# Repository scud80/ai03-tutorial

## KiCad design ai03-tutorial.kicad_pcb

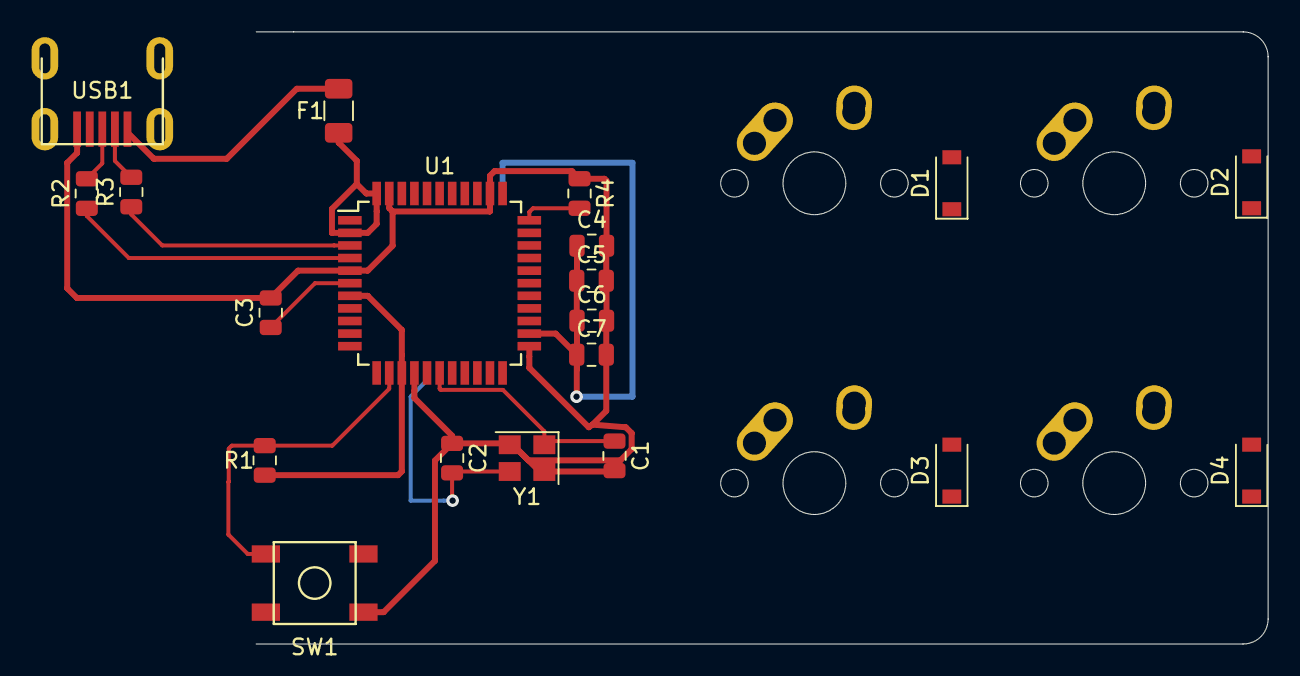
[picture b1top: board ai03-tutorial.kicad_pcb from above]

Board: 2 copper layers, 64.3 x 38.9 mm, 24 parts (0 on the bottom side), 20 nets.

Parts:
C1, C2: 22pF; C_0805_2012Metric
C3: 1μF; C_0805_2012Metric
C4, C5, C6: 0.1μF; C_0805_2012Metric
C7: 10μF; C_0805_2012Metric
D1, D2, D3, D4: D_Small; D_SOD-123
F1: 500mA; Fuse_1206_3216Metric
MX1, MX2, MX3, MX4: MX-NoLED; MX-1U-NoLED
R1, R4: 10k; R_0805_2012Metric
R2, R3: 22; R_0805_2012Metric
SW1: SW_Push; SKQG-1155865
U1: ATmega32U4-AU; TQFP-44_10x10mm_P0.8mm
USB1: Molex-0548190589
Y1: 16MHz; Crystal_SMD_3225-4Pin_3.2x2.5mm

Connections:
+5V: C4.1, C5.1, C6.1, C7.1, F1.1, R1.1, U1.2, U1.7, U1.14, U1.24, U1.34, U1.44
COL0: MX1.1, MX3.1
COL1: MX2.1, MX4.1
D+: R2.2, USB1.3
D-: R3.2, USB1.4
GND: C1.2, C2.1, C3.2, C4.2, C5.2, C6.2, C7.2, R4.1, SW1.1, U1.5, U1.15, U1.23, U1.35, U1.43, USB1.1, Y1.2, Y1.4
unnamed: C1.1, U1.17, Y1.1
unnamed: C2.2, U1.16, Y1.3
unnamed: C3.1, U1.6
unnamed: D1.2, MX1.2
unnamed: D2.2, MX2.2
unnamed: D3.2, MX3.2
unnamed: D4.2, MX4.2
unnamed: R1.2, SW1.2, U1.13
unnamed: R2.1, U1.4
unnamed: R3.1, U1.3
unnamed: R4.2, U1.33
ROW0: D1.1, D2.1
ROW1: D3.1, D4.1
VCC: F1.2, USB1.5

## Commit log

2020-02-10 Initialization
2020-02-10 Add submodules
2020-02-11 schematic done
2020-02-13 pcb mostly done
